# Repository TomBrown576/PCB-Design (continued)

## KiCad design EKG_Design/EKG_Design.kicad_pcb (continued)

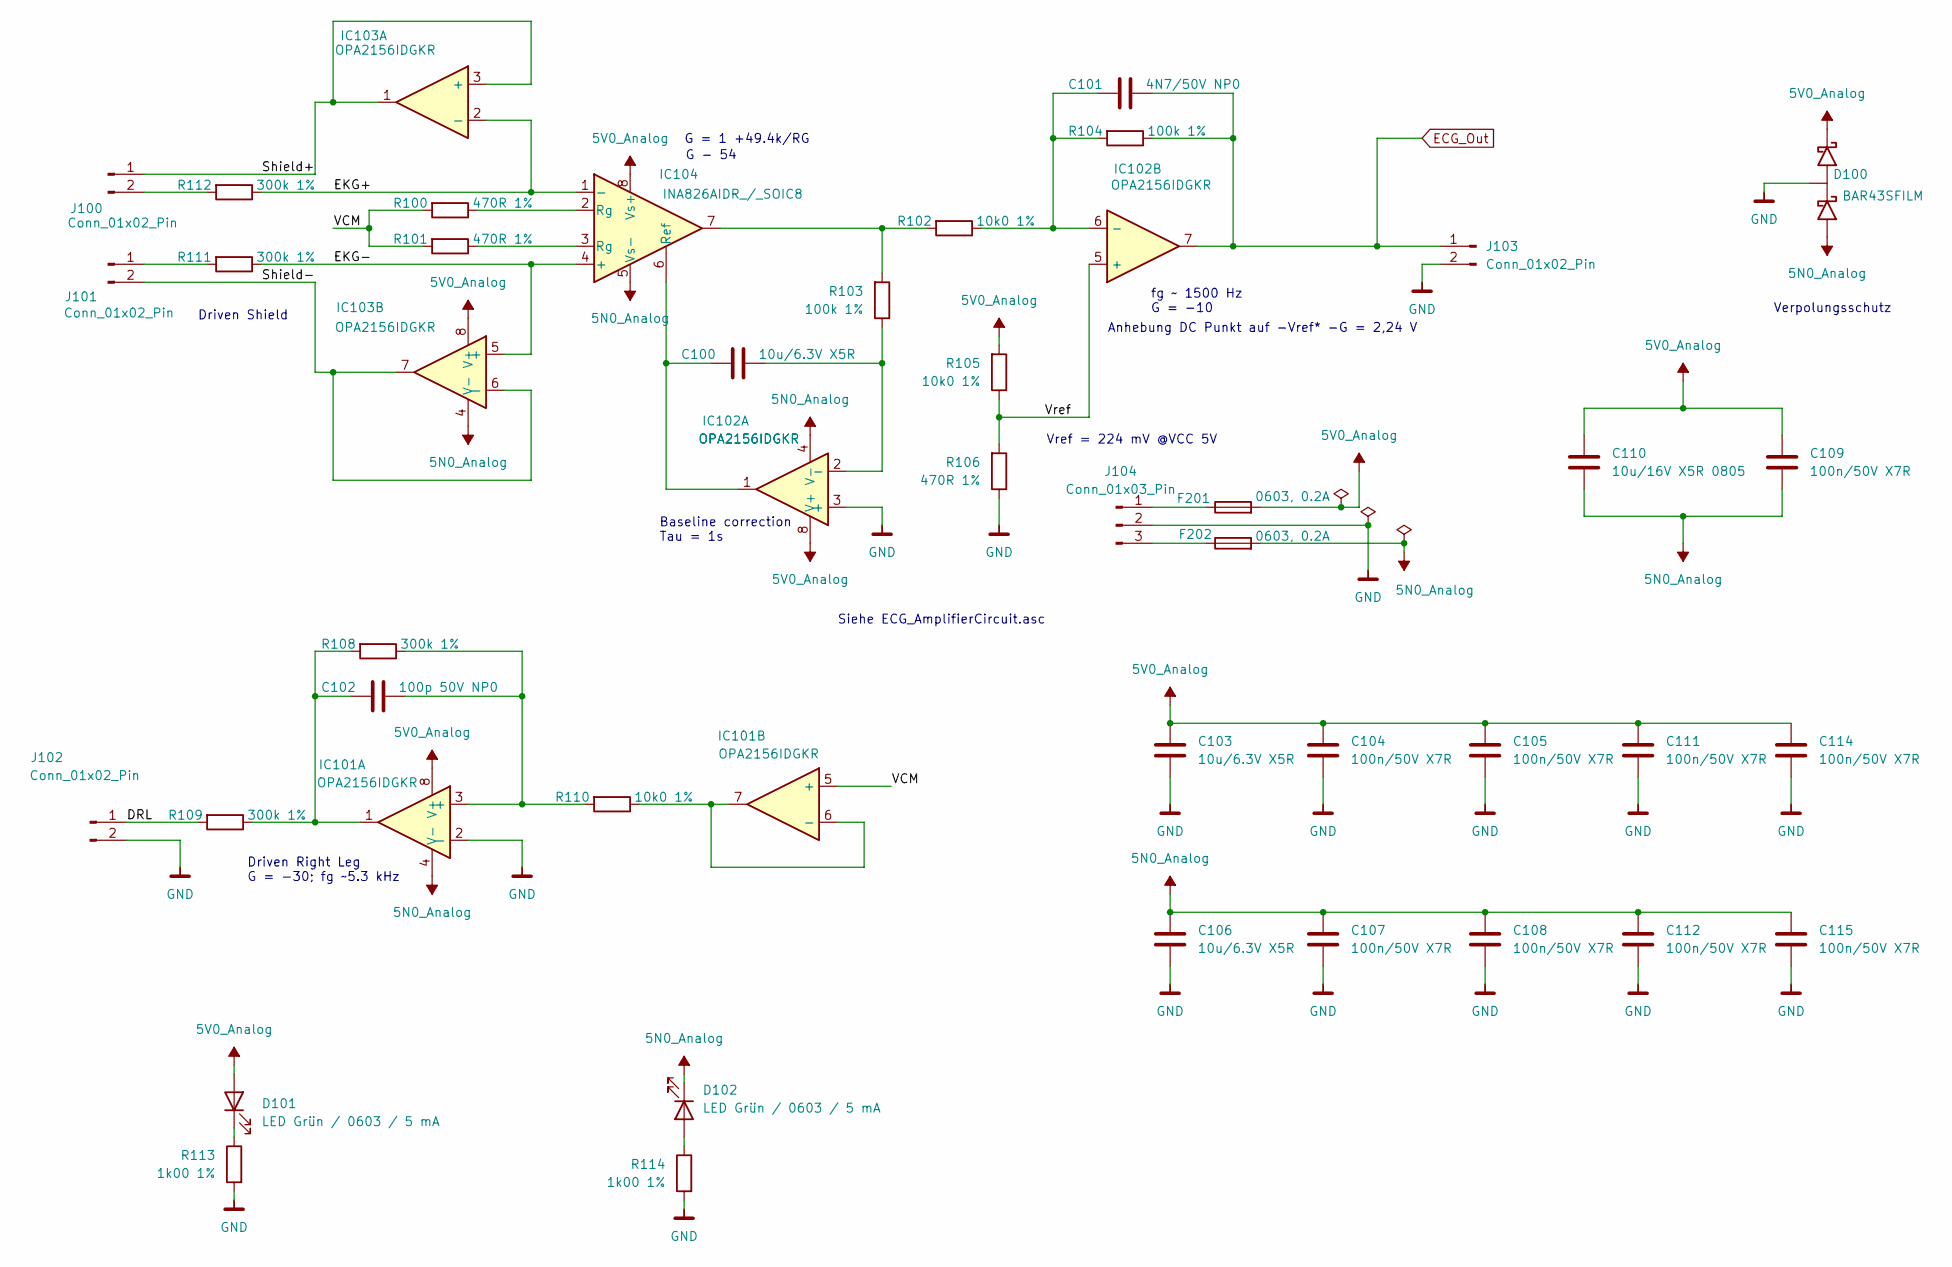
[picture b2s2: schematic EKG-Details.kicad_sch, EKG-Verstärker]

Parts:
C100, C103, C106: 10u/6.3V X5R; C_0603_1608Metric_Pad1.08x0.95mm_HandSolder
C101: 4N7/50V NP0; C_0603_1608Metric_Pad1.08x0.95mm_HandSolder
C102: 100p 50V NP0; C_0603_1608Metric_Pad1.08x0.95mm_HandSolder
C104, C105, C107, C108, C109, C111, C112, C114, C115: 100n/50V X7R; C_0603_1608Metric_Pad1.08x0.95mm_HandSolder
C110: 10u/16V X5R 0805; C_0603_1608Metric_Pad1.08x0.95mm_HandSolder
D100: BAR43SFILM; SOT-23
D101, D102: LED Grün / 0603 / 5 mA; LED_0603_1608Metric_Pad1.05x0.95mm_HandSolder
F201, F202: 0603, 0.2A; Fuse_0603_1608Metric_Pad1.05x0.95mm_HandSolder
IC101, IC102, IC103: OPA2156IDGKR; VSSOP-8_3x3mm_P0.65mm
IC104: INA826AIDR_/_SOIC8; SOIC-8_3.9x4.9mm_P1.27mm
J100, J101, J102, J103: Conn_01x02_Pin; PinHeader_1x02_P2.54mm_Vertical
J104: Conn_01x03_Pin; PinHeader_1x03_P2.54mm_Vertical
R100, R101, R106: 470R 1%; R_0603_1608Metric_Pad0.98x0.95mm_HandSolder
R102, R105, R110: 10k0 1%; R_0603_1608Metric_Pad0.98x0.95mm_HandSolder
R103, R104: 100k 1%; R_0603_1608Metric_Pad0.98x0.95mm_HandSolder
R108, R109, R111, R112: 300k 1%; R_0603_1608Metric_Pad0.98x0.95mm_HandSolder
R113, R114: 1k00 1%; R_0603_1608Metric_Pad0.98x0.95mm_HandSolder

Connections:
5N0_Analog: C106.1, C107.1, C108.1, C109.2, C110.2, C112.1, C115.1, D100.1 (A), D102.1 (K), F202.2, IC101.4 (V-), IC102.4 (V-), IC103.4 (V-), IC104.5 (Vs-)
5V0_Analog: C103.1, C104.1, C105.1, C109.1, C110.1, C111.1, C114.1, D100.3 (C), D101.2 (A), F201.2, IC101.8 (V+), IC102.8 (V+), IC103.8 (V+), IC104.8 (Vs+), R105.2; also elsewhere on the board
/EKG-Details/DRL: J102.1, R109.2
/EKG-Details/EKG+: IC103.2 (-), IC104.1 (-), R112.1
/EKG-Details/EKG-: IC103.5 (+), IC104.4 (+), R111.1
/EKG-Details/Shield+: IC103.1, IC103.3 (+), J100.1
/EKG-Details/Shield-: IC103.6 (-), IC103.7, J101.2
/EKG-Details/VCM: IC101.5 (+), R100.2, R101.2
/EKG-Details/Vref: IC102.5 (+), R105.1, R106.2
ECG_Out: C101.1, IC102.7, J103.1, R104.1; also elsewhere on the board
GND: C103.2, C104.2, C105.2, C106.2, C107.2, C108.2, C111.2, C112.2, C114.2, C115.2, D100.2 (B), IC101.2 (-), IC102.3 (+), J102.2, J103.2, J104.2, R106.1, R113.2, R114.2; also elsewhere on the board
unnamed: C102.2, IC101.1, R108.2, R109.1
unnamed: D101.1 (K), R113.1
unnamed: D102.2 (A), R114.1
unnamed: C102.1, IC101.3 (+), R108.1, R110.2
unnamed: IC101.6 (-), IC101.7, R110.1
unnamed: C100.1, IC102.2 (-), R103.1
unnamed: C101.2, IC102.6 (-), R102.1, R104.2
unnamed: IC104.7, R102.2, R103.2
unnamed: C100.2, IC102.1, IC104.6 (Ref)
unnamed: IC104.2 (Rg), R100.1
unnamed: IC104.3 (Rg), R101.1
unnamed: J100.2, R112.2
unnamed: J101.1, R111.2
unnamed: F201.1, J104.1
unnamed: F202.1, J104.3

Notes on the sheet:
Vref = 224 mV @VCC 5V
G = 1 +49.4k/RG
Driven Shield
Driven Right Leg G = -30; fg ~5.3 kHz
Baseline correction Tau = 1s
Verpolungsschutz
Anhebung DC Punkt auf -Vref* -G = 2,24 V
G - 54
Siehe ECG_AmplifierCircuit.asc
fg ~ 1500 Hz G = -10

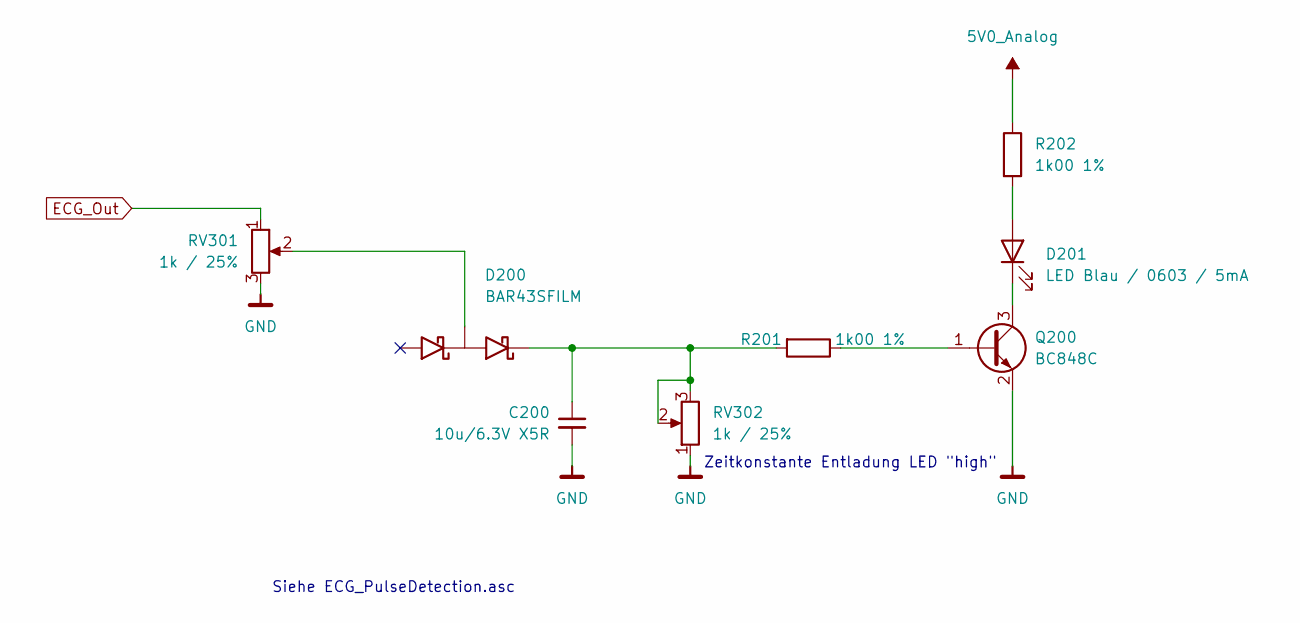
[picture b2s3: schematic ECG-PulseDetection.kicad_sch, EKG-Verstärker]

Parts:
C200: 10u/6.3V X5R; C_0603_1608Metric_Pad1.08x0.95mm_HandSolder
D200: BAR43SFILM; SOT-23
D201: LED Blau / 0603 / 5mA; LED_0603_1608Metric_Pad1.05x0.95mm_HandSolder
Q200: BC848C; SOT-23
R201, R202: 1k00 1%; R_0603_1608Metric_Pad0.98x0.95mm_HandSolder
RV301, RV302: 1k / 25%; Potentiometer_Bourns_TC33X_Vertical

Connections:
5V0_Analog: R202.1; also elsewhere on the board
ECG_Out: RV301.1; also elsewhere on the board
GND: C200.2, Q200.2 (E), RV301.3, RV302.1; also elsewhere on the board
unnamed: D200.2 (B), RV301.2
unnamed: C200.1, D200.3 (C), R201.2, RV302.2, RV302.3
unnamed: D201.2 (A), R202.2
unnamed: D201.1 (K), Q200.3 (C)
unnamed: Q200.1 (B), R201.1

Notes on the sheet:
Zeitkonstante Entladung LED "high"
Siehe ECG_PulseDetection.asc

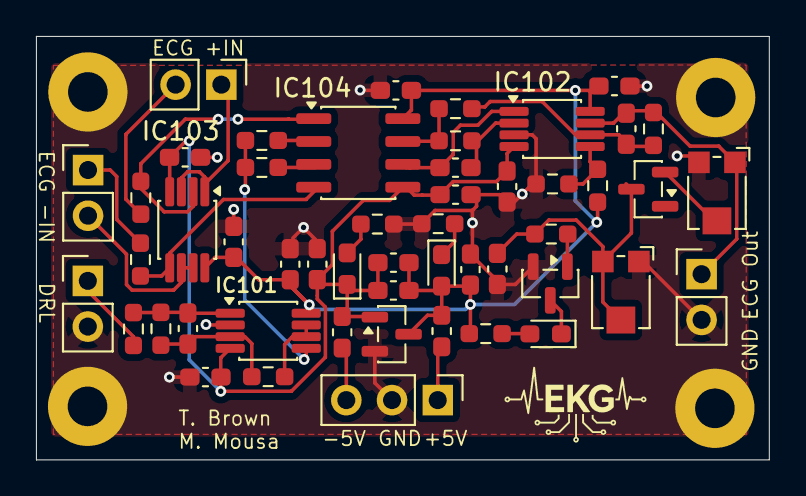
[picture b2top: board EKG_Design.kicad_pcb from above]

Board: 2 copper layers, 40.7 x 23.5 mm, 55 parts (0 on the bottom side), 31 nets.

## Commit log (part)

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2026-04-20 initial EKG file created
2026-04-20 changed filename
2026-04-20 Started EKG-Details and ECG-PulseDetection Circuit Symbols implemented
2026-04-20 EKG-Details updated
2026-04-20 EKG-Details basic schematic, still needs cleaning
2026-04-21 EKG-Details basic schematic, still needs a little cleaning
2026-05-03 Finished EKG Schematic
2026-05-04 updated AM Receiver Symbols and schematic. Only need 74HCT4046 & SFD455
2026-05-04 Updated AM Receiver Schematic with all Symbols. Footprint, manifest and data sheet still needed
2026-05-16 Finished ECG Schematic and finished laying out the PCB
2026-05-16 Finished ECG Routing
2026-05-18 adjusted board properties and added manifest items
2026-05-28 Updated min clearance mistake to solve DRC errors
2026-05-28 added logo to Schematic
2026-05-28 Added Symbol libraries
2026-05-28 added 3d model for Poti
2026-05-28 Added GND zone to front of the board
2026-05-28 added ibom and jobsets
2026-05-28 Cleaned layers
2026-05-29 Added Sheet details to info box on PCB
2026-05-29 fixed a new DRC error
2026-06-01 fixed the remaining DRC and ERC errors
2026-06-01 update ibom
2026-06-01 Cleared all DRC issues
